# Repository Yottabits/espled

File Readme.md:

# ESP-LED - the ultimate LED-Strip-Controller-Board!

## What can it do?
* Controle RGB-LED strip (12V Mode)
* Controle RGBWW-LED strips (12V Mode)
* Controle WW LED-Strips (12V Mode)
* Controle WS2812 individually adressable LED Strips (5V Mode)
* Controle APA102 individually adressable LED Strips (5V Mode)
* Communicate over WiFi + MQTT
* Measure surrounding Temperature
* Sound-2-Light trough integrated Microphone

## How does it look like?

## How does the Pinning look like?

## How to use it?

### How to use it in 12V Mode with RGBWW
Hardware:
* You only need to insert as many MOSFETS (IRLZ34N) as you want to controle Channels. Bridge the jumpers according to the table below

Software:
* Boot into configuration mode (see software README) and change the "LED Type" to "RGB", "RGBW" or "RGBWW" for 3, 4 or 5 active channels.

### How to use it in 5V Mode with WS2812
Hardware:
* Just bridge the Jumpers according to the table below.

Software:
* Boot into configuration mode (see software README) and change the "LED Type" to "WS2812".

### How to use it in 5V Mode with APA102
Hardware:
* Just bridge the Jumpers according to the table below.

Software:
* Boot into configuration mode (see software README) and change the "LED Type" to "APA102".

## What controle the Jumpers?
| Jumpernumber | Connects-Between | Function         |
|--------------|------------------|------------------|
|       1      |Q1 Signal - Q1 Out| WS2812, APA102                  |
|       2      |Q2 Signal - Q2 Out| APA102           |
|       3      |Q3 Signal - Q3 Out|                  |
|       4      |Q4 Signal - Q4 Out|                  |
|       5      |Q5 Signal - Q5 Out|                  |
|       6      |   IO13 - Q1      | RGB, RGBW, RGBWW |
|       7      |   IO12 - Q2      | RGB, RGBW, RGBWW |
|       8      |   IO14 - Q3      | RGB, RGBW, RGBWW |
|       9      |   IO16 - Q4      | RGBW, RGBWW      |
|      10      |   IO5 - Q5       | RGBWW            |

## Which parts do I need?
See the Bill-Of-Materials file named ESPLED.csv in the hardware folder.

## Supported Modes
See Wiki (https://github.com/Yottabits/espled/wiki/Modes-Description)

## nice Projects with led animations for insperation
* GoodListOfAnimations for individually addressable strips: https://www.tweaking4all.com/hardware/arduino/arduino-all-ledstrip-effects-in-one/
* https://github.com/Aircoookie/WLED/wiki

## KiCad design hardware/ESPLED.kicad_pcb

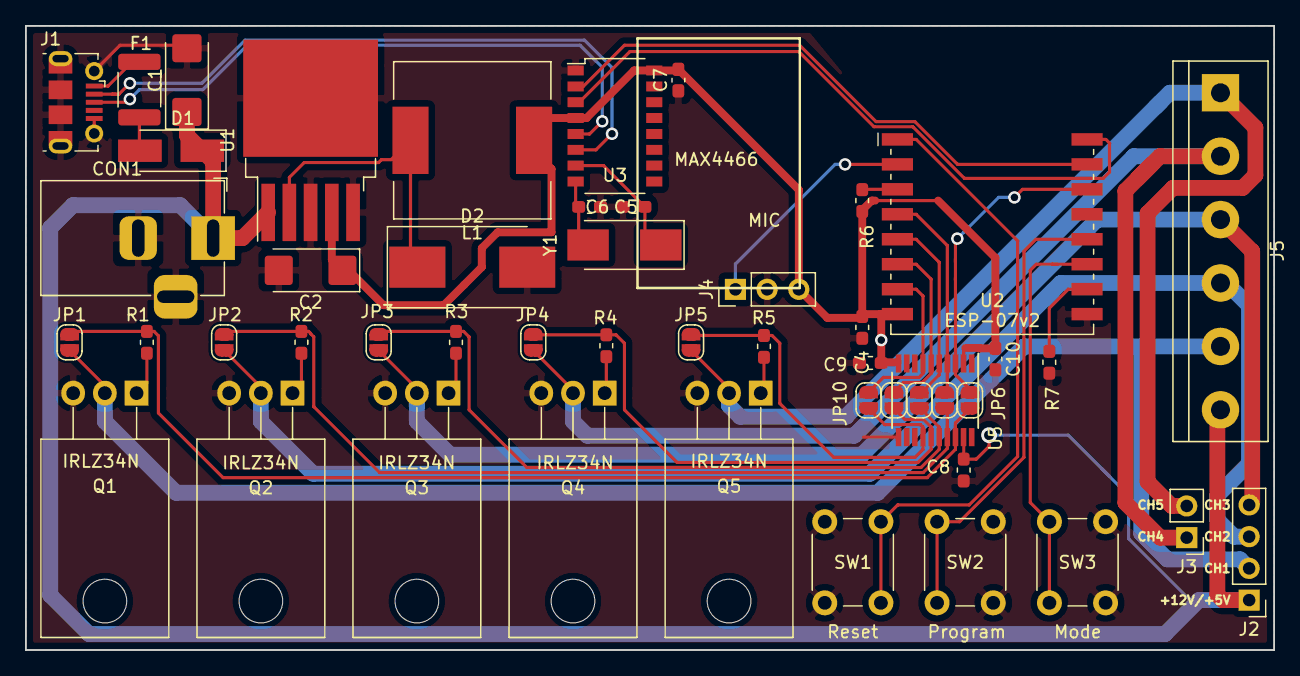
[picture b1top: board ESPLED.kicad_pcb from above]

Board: 2 copper layers, 100.0 x 50.0 mm, 49 parts (0 on the bottom side), 38 nets.

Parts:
C1: 680uF; CP_EIA-6032-20_AVX-F_Pad2.25x2.35mm_HandSolder
C2: 220uF; CP_EIA-6032-20_AVX-F_Pad2.25x2.35mm_HandSolder
C4, C8, C9: 100nF; C_0603_1608Metric_Pad1.05x0.95mm_HandSolder
C5, C6: 22p; C_0603_1608Metric_Pad1.05x0.95mm_HandSolder
C7: 100n; C_0603_1608Metric_Pad1.08x0.95mm_HandSolder
C10: 100nF; C_0603_1608Metric_Pad1.08x0.95mm_HandSolder
CON1: BARREL_JACK; BarrelJack_Horizontal
D1: 1N5817; D_SMA_Handsoldering
D2: 1N5825; D_SMC_Handsoldering
F1: Polyfuse; Fuse_1812_4532Metric_Pad1.30x3.40mm_HandSolder
J1: USB_B_Micro; USB_Micro-B_Molex-105017-0001
J2: LED_CON_RGB; PinHeader_1x04_P2.54mm_Vertical
J3: LED_CON_WW; PinHeader_1x02_P2.54mm_Vertical
J4: MIC; PinHeader_1x03_P2.54mm_Vertical
J5: Conn_01x06; TerminalBlock_bornier-6_P5.08mm
JP1, JP2, JP3, JP4, JP5, JP6, JP7, JP8, JP9, JP10: GPIO LINK; SolderJumper-2_P1.3mm_Open_RoundedPad1.0x1.5mm
L1: 33uH; L_12x12mm_H8mm
Q1, Q2, Q3, Q4, Q5: IRLZ34N; TO-220-3_Horizontal_TabDown
R1, R2, R3, R4, R5: 100; R_0603_1608Metric_Pad1.05x0.95mm_HandSolder
R6, R7: 10k; R_0603_1608Metric_Pad1.05x0.95mm_HandSolder
SW1: Reset; SW_PUSH_6mm
SW2: Program; SW_PUSH_6mm
SW3: Mode; SW_PUSH_6mm
U1: LM2596T-3.3; TO-263-5_TabPin3
U2: ESP-07v2; ESP-07
U3: INTERFACE-CH340G; SOP-16_4.4x10.4mm_P1.27mm
U5: TXS0108EPW; TSSOP-20_4.4x6.5mm_P0.65mm
Y1: Crystal; Crystal_SMD_0603-2Pin_6.0x3.5mm_HandSoldering

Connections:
+3V3: C2.1, C4.2, C7.2, C9.2, C10.1, J4.3, L1.1, R6.1, U1.4, U2.8, U3.4, U3.16, U5.2, U5.10
+12V: C1.1, C8.1, CON1.1, D1.1, J2.1, J5.6, U1.1, U5.19
/CH1: J2.2, J5.5, JP1.1, Q1.2
/CH2: J2.3, J5.4, JP2.1, Q2.2
/CH3: J2.4, J5.3, JP3.1, Q3.2
/CH4: J3.1, J5.2, JP4.1, Q4.2
/CH5: J3.2, J5.1, JP5.1, Q5.2
GND: C1.2, C2.2, C4.1, C5.2, C6.2, C7.1, C8.2, C9.1, C10.2, CON1.2, CON1.3, D2.2, J1.5, J1.6, J4.2, Q1.3, Q2.3, Q3.3, Q4.3, Q5.3, R7.2, SW1.1, SW2.2, SW3.2, U1.3, U1.5, U2.9, U3.1, U5.11
HSIG1: JP1.2, JP6.1, R1.2, U5.18
HSIG2: JP2.2, JP7.1, R2.2, U5.17
HSIG3: JP3.2, JP8.1, R3.2, U5.16
HSIG4: JP4.2, JP9.1, R4.2, U5.15
HSIG5: JP5.2, JP10.1, R5.2, U5.14
unnamed: C5.1, U3.8, Y1.2
unnamed: C6.1, U3.7, Y1.1
unnamed: D1.2, F1.1
unnamed: D2.1, L1.2, U1.2
unnamed: J1.2, U3.6
unnamed: J1.3, U3.5
unnamed: J4.1, U2.2
unnamed: Q1.1, R1.1
unnamed: Q2.1, R2.1
unnamed: Q3.1, R3.1
unnamed: Q4.1, R4.1
unnamed: Q5.1, R5.1
unnamed: R6.2, U2.3
unnamed: R7.1, U2.10
unnamed: SW1.2, U2.1
unnamed: SW2.1, U2.12
unnamed: SW3.1, U2.11
RXD: U2.15, U3.2
SIG1: JP6.2, U2.14, U5.3
SIG2: JP7.2, U2.4, U5.4
SIG3: JP8.2, U2.5, U5.5
SIG4: JP9.2, U2.6, U5.6
SIG5: JP10.2, U2.7, U5.7
TXD: U2.16, U3.3
VUSB: F1.2, J1.1

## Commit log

2018-11-24 Init: Version 2: external programmer, mosfet pinout fix
2018-11-24 All coponents set
2018-11-24 Added power suply switching circuit, cleaned up
2018-11-24 First PCB Layout generated. TODO: Screw terminal fix
2018-11-26 Added caps for crystal
2018-11-26 Schematic done. Next: Fottprint research
2019-01-07 Footprint research done, layout more or less gelayoutet
2019-01-07 Ongoin reordering. Will probably
2019-01-08 Routing done! Next step: verification
2019-01-14 layout finished. Adding logic level converter
2019-01-14 Go to gitlab
2019-01-14 started doku
2019-01-14 doku images
2019-01-14 doku
2019-01-14 Logic Level Converter added. Schematic finished
2019-01-15 Routed
2019-01-15 Layout added to docs
2019-01-15 schematic pdf added
2019-01-15 rotated pdf
2019-01-15 new 3d üreview
2019-01-16 adjusted position of marking
2019-01-16 gerber addedededed
2019-01-17 final 01:11
2019-01-17 gerber final
2019-01-17 added qrcode as bmp and png
2019-03-04 rearranges structure
2019-03-04 rearranged
2019-03-04 fixed dir
2019-03-04 added software
2019-03-04 removed copy of different project
2019-03-04 added pwm submodule
2019-03-04 integrated mqtt and WiFiClient
2019-03-17 software manual created
2019-03-18 Edited docs
2019-03-28 Update Readme.md
    Added mode table with some modes
2019-03-28 deleted some blanks2
2019-03-28 added some more modes
2019-04-18 dome
2019-05-28 changed something...
2019-05-28 cleaned one line
2019-05-28 Code is compiling again
2019-05-28 Added StripControle Class
2019-05-28 edited some stuff
2019-05-28 Working WiFiManager with custom Parameters
2019-05-28 Changed DEVNOTES
2019-05-28 Bitte sei wieder der MASTER
2019-05-28 created files for AnnimationHandlers
2019-05-28 Renamed MQTT connect and created varSilo
2019-05-28 less byte, more char
2019-11-06 Changed README.md to get back on track
2019-11-06 Added Jumper functions to README
2019-11-07 Added BOM
2019-11-07 removed tmp files
2020-03-18 added vscode folder to .gitignore file
2020-04-14 Edit README and experimental pwm library
2020-04-14 added json parsing
2020-04-14 Add warning for mqtt message length
2020-04-14 Move typedefs to seperate header file (and fix missing semicolon)
2020-04-14 add new format of Animation Handler
2020-04-15 Move pindefs to seperate header file
2020-04-15 Implement StripControle functions
2020-04-15 try to implement Fade Animation
2020-04-15 Add stripType to defs, animationHanler + stripController initialized
2020-04-15 add runAnnimationHandler Function (in loop)
2020-04-15 add new mode files
2020-04-15 add footprint of handler function
2020-04-15 update Annimation Handlers description
2020-04-15 Add blueprints of modes and implementation of fade2Color (which is not yet finally working)
2020-04-15 implement Annimation handler class
2020-04-15 add type Definitions according to our needs
2020-04-15 update stripControle Class
2020-04-15 make main work with Annimation Handler Class and add initialization of different Pointers
2020-04-15 add Modes folder
2020-04-15 prepare...
2020-04-15 Add missing includes to AnimationHandlerBus
2020-04-15 mi abend krasse verzweiflung
2020-04-15 for fixing board :*?
2020-04-16 Implement Debug over MQTT function
2020-04-16 Fix Mode 0 (Fade)
2020-04-16 Switch to OTA Updates
2020-04-16 added some comments in blinkColor.cpp
2020-04-16 changed names to enable FASTLED import -> RGB enum used multiple times
2020-04-16 added LogLevel Argument to Debug Function
2020-04-16 Implement MQTT Debug
2020-04-16 Test MQTT Debug
2020-04-16 solved mistake which stopped compiling
2020-04-16 compiling state dome
2020-04-16 updated debugging code to new debugFKT
2020-04-16 add debugging of analogRead of Mic
2020-04-16 Replace Serial with Debug functon
2020-04-16 correct typo in debug fkt
2020-04-16 changed port
2020-04-16 Debug all messages
2020-04-16 add hmoas
2020-04-16 Fix ADC read
2020-04-16 Shorten debug message on new mqtt messages
2020-04-16 move debugFkt so it only prints something during the fade
2020-04-16 Fixes #2
2020-04-17 Fix Pin Definiton Swap (CW WW)
2020-04-17 Fix MQTT message scrambling (Debug function interferred)
2020-04-17 Add breathe mode prototype
2020-04-17 Fix yet another CW WW swap
2020-04-17 Working state of breathe mode (needs a lot of cleanup)
2020-04-17 First compiling state with new AnimationHandler Class
2020-04-17 Finish class rewrite, ready for testing
2020-04-17 Move HSV2RGB and RGB2HSV to AnimationHandler
2020-04-17 Remove unnecessary includes and fix IP print
2020-04-17 Remove breathe conversion overhead and fix #15
2020-04-17 MQTT message queue: Apply only changed values
2020-04-18 Add sound sampling from mic using a ringbuffer
2020-04-18 Remove unused HSV Container
2020-04-18 Working FFT in sound2light
2020-04-18 Add missing dependency: arduinoFFT Change upload port to OTA test device
2020-04-19 fixxed ip adress displaying in initWifi
2020-04-19 write some description and example jsons for different modes
2020-04-19 change code block
2020-04-19 added json block
2020-04-19 extend documentation for different modes
2020-04-19 Update Readme.md
    added another link with annimations
2020-04-19 Update Readme.md
    Moved ToDo list to issiues
2020-04-19 implement and document strobe mode - test is missing
2020-04-19 not only debug also cathc error
2020-04-19 removed equal signs at the wrong spot xD
2020-04-19 changed cw ww order to be consistent
2020-04-19 Fix strobe()
2020-04-19 Introduce advanced debug features(cycle count, free heap) and configurable pwmFrequency
2020-04-28 fix issue #17 and catch possible undefined states
2020-04-28 resolve #22 - initMQTT now publishes a message under the /ESPLED/ on each mqtt connect
2020-04-28 Reconnect MQTT + reenable debug. Fix #6
2020-04-28 disable ring buffer, change debug log level in breathe()
2020-04-28 Change Capacitor size, fix #23 move C4 near ESP8266, fix #11 change label P1 to P3, fix #12
2020-04-28 Implement MQTT reconnect timeout
2020-04-28 current status dome
2020-04-28 Add Backup of pcb
2020-04-28 Move Microphone handling to new class
2020-04-28 Initiate micHandler instance in main
2020-04-29 run micHandler and integrate system_adc_read()
2020-04-29 implementet mqtt secure functionality
2020-04-29 fix bug in check
2020-04-29 change platformio ini
2020-05-02 Experimental DHT11
2020-05-02 Remove MQTT topic generation from initWifi + timing fix in initMQTT
2020-05-02 Remove unused PWM Library
2020-05-02 split main.cpp in multiple files
2020-05-06 christian zufriedenstellen
2020-05-07 add comments and improve formatting
2020-05-07 add comments
2020-05-07 implement blink mode + persistent var silo
2020-05-07 Transmit temp and humidity data
2020-05-08 Remove debug message
2020-05-08 Part fix blink
2020-05-12 set main and debug topic in initWifi instead of initMqtt
2020-05-12 Send MQTT debug only if connected
2020-05-20 descriptions and blink function
2020-10-14 Sensor fix
2020-10-14 Uniquify Mqtt identifier
2020-10-19 Update README.md
    Explain reset procedure to format spiffs
2020-10-19 Remove debug message in wrong topic
2020-10-19 Simplify reset procedure
2020-10-19 Fixes #9
2020-10-19 Remove unused validation on silo->length
2020-10-20 Add Industrial Flicker no Implementation yet
2020-10-20 Finalized industrialFlicker with duration as parameter, working super smooth
2020-10-23 deleted flicker on state
2020-10-23 reformatted file
2020-10-23 Fix Compiler Warning because no return is made in default case
2020-10-23 reformat
2020-10-23 Added some code not working yet
2020-10-25 Move Folder modes -> UniformModes
2020-10-25 Add Parameter Strip Length in wifi manager
2020-10-25 Implement Bus functionality and add first mode wipe
2020-10-25 Add var strip_length into which we save the wifimanager parameter strip_length
2020-10-25 Implement Wipe Mode
2020-10-25 Mark Task
2020-10-25 Add first idea of noise mode
2020-10-25 correct prev commit
2020-10-25 add vuMeter file
2020-10-25 AddTask in Code
2020-10-25 add some unsigneds against warnings
2020-10-25 move platformio to gitignore
2020-10-25 remove platformio.ini
2020-10-25 handle -1 standard value and process error state
2020-10-25 solved ini file problems finally
2020-10-25 kind of working, crashes, oldColor must be handled
2020-10-26 Changed typeDefinition Caps formating
2020-10-26 add define
2020-10-26 Add Variable for RGB order
2020-10-26 doch nich
2020-10-26 add comment for RGB GRB problem - hint maybe add new type
2020-10-26 Change strip type to pointer, implement APA102 AnimationHandler
2020-10-26 Add default case for bus initialization and add debug messages
2020-10-26 solve oldColor Problem for Adressable Strips
2020-10-26 made adressable modes working without bugs
2020-10-29 printVector working without arguments
2020-10-29 vuMeter test
2020-10-29 Increase audio buffer and add debug to vuMeter
2020-10-29 repair system debug function
2020-10-29 Use cycle count instead of millis() for time measurement. Reduce samples
2020-11-01 Remove FFT from vuMeter
2020-11-01 Implement getFrequency function
2020-11-02 Add position to vuMeter
2022-02-10 * Remove Temp Sensor * Redo Power Part -> Replace AMS1117 with LM2596 StepDown IC + Peripherals * Redo PCB * Replace Wrong Screw Terminal * Add aditional C10 close to OE of U5
2022-09-10 unknown changes
2022-09-10 some random changes
